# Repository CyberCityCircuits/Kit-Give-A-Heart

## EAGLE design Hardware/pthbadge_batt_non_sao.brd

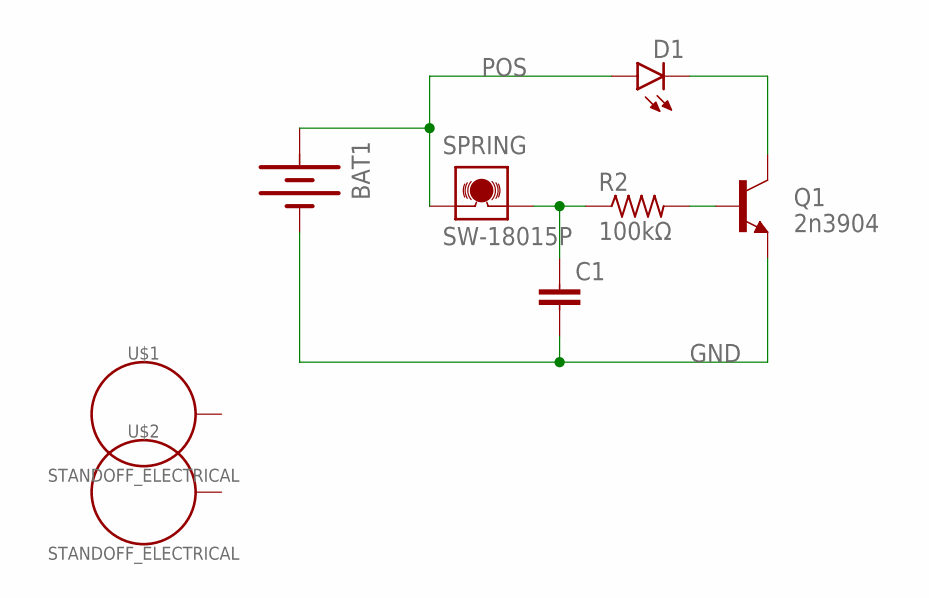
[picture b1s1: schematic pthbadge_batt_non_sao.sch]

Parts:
BAT1: BATTERY20PTH; BATTCOM_20MM_PTH
C1: CAPPTH; CAP-PTH-SMALL
D1: LED5MM
Q1: 2n3904; TO-92
R2: 100kΩ; 0207/10
SPRING: SW-18015P
U$1, U$2: STANDOFF_ELECTRICAL; STANDOFF-ELECTRICAL

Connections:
BASE: Q1.2 (B), R2.2
GND: BAT1.2 (-), C1.2, Q1.1 (E)
unnamed: D1.K (C), Q1.3 (C)
unnamed: C1.1, R2.1, SPRING.2
POS: BAT1.1 (+), D1.A, SPRING.1

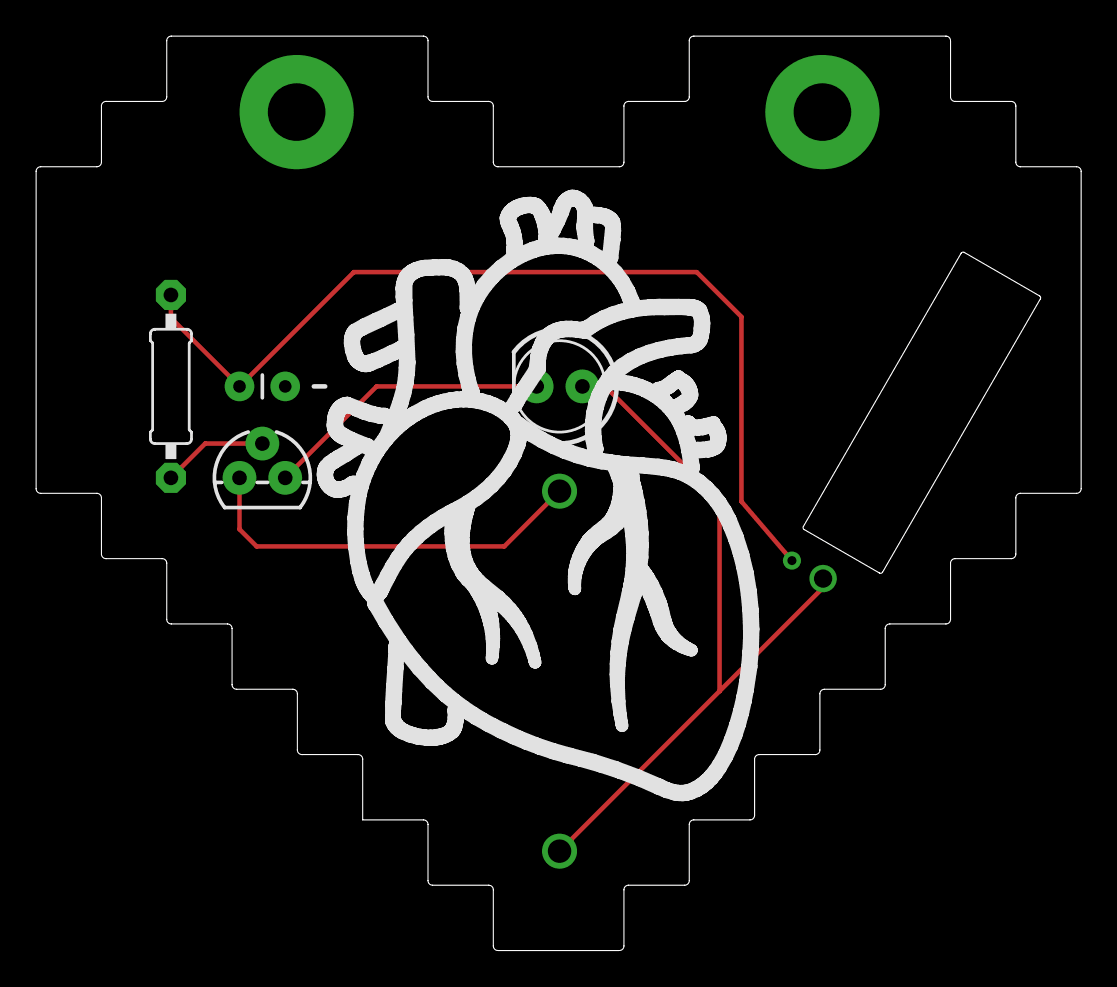
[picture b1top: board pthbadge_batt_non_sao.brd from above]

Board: 2 copper layers, 58.0 x 50.8 mm, 8 parts (1 on the bottom side), 5 nets.

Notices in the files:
parts and their libraries:
SparkFun-LED: Licensing: Creative Commons ShareAlike 4.0 International - https://creativecommons.org/licenses/by-sa/4.0
